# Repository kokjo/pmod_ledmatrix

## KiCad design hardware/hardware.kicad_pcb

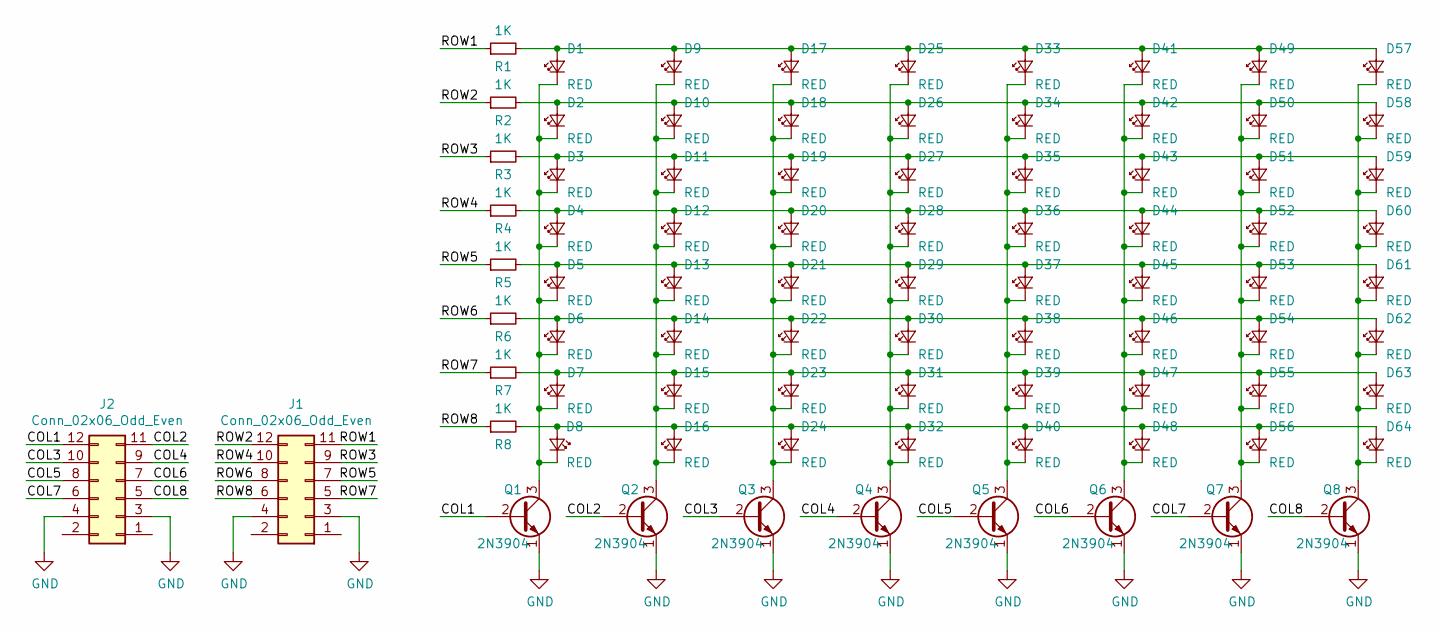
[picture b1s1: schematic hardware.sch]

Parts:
D1, D2, D3, D4, D5, D6, D7, D8, D9, D10, D11, D12, D13, D14, D15, D16, D17, D18, D19, D20, D21, D22, D23, D24, D25, D26, D27, D28, D29, D30, D31, D32, D33, D34, D35, D36, D37, D38, D39, D40, D41, D42, D43, D44, D45, D46, D47, D48, D49, D50, D51, D52, D53, D54, D55, D56, D57, D58, D59, D60, D61, D62, D63, D64: RED; D_0603_1608Metric
J1, J2: Conn_02x06_Odd_Even; PinHeader_2x06_P2.54mm_Horizontal
Q1, Q2, Q3, Q4, Q5, Q6, Q7, Q8: 2N3904; SOT-23
R1, R2, R3, R4, R5, R6, R7, R8: 1K; R_0603_1608Metric

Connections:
/COL1: J2.12, Q1.2 (B)
/COL2: J2.11, Q2.2 (B)
/COL3: J2.10, Q3.2 (B)
/COL4: J2.9, Q4.2 (B)
/COL5: J2.8, Q5.2 (B)
/COL6: J2.7, Q6.2 (B)
/COL7: J2.6, Q7.2 (B)
/COL8: J2.5, Q8.2 (B)
/ROW1: J1.11, R1.1
/ROW2: J1.12, R2.1
/ROW3: J1.9, R3.1
/ROW4: J1.10, R4.1
/ROW5: J1.7, R5.1
/ROW6: J1.8, R6.1
/ROW7: J1.5, R7.1
/ROW8: J1.6, R8.1
GND: J1.3, J1.4, J2.3, J2.4, Q1.1 (E), Q2.1 (E), Q3.1 (E), Q4.1 (E), Q5.1 (E), Q6.1 (E), Q7.1 (E), Q8.1 (E)
unnamed: D1.1 (K), D2.1 (K), D3.1 (K), D4.1 (K), D5.1 (K), D6.1 (K), D7.1 (K), D8.1 (K), Q1.3 (C)
unnamed: D1.2 (A), D9.2 (A), D17.2 (A), D25.2 (A), D33.2 (A), D41.2 (A), D49.2 (A), D57.2 (A), R1.2
unnamed: D9.1 (K), D10.1 (K), D11.1 (K), D12.1 (K), D13.1 (K), D14.1 (K), D15.1 (K), D16.1 (K), Q2.3 (C)
unnamed: D2.2 (A), D10.2 (A), D18.2 (A), D26.2 (A), D34.2 (A), D42.2 (A), D50.2 (A), D58.2 (A), R2.2
unnamed: D3.2 (A), D11.2 (A), D19.2 (A), D27.2 (A), D35.2 (A), D43.2 (A), D51.2 (A), D59.2 (A), R3.2
unnamed: D4.2 (A), D12.2 (A), D20.2 (A), D28.2 (A), D36.2 (A), D44.2 (A), D52.2 (A), D60.2 (A), R4.2
unnamed: D5.2 (A), D13.2 (A), D21.2 (A), D29.2 (A), D37.2 (A), D45.2 (A), D53.2 (A), D61.2 (A), R5.2
unnamed: D6.2 (A), D14.2 (A), D22.2 (A), D30.2 (A), D38.2 (A), D46.2 (A), D54.2 (A), D62.2 (A), R6.2
unnamed: D7.2 (A), D15.2 (A), D23.2 (A), D31.2 (A), D39.2 (A), D47.2 (A), D55.2 (A), D63.2 (A), R7.2
unnamed: D8.2 (A), D16.2 (A), D24.2 (A), D32.2 (A), D40.2 (A), D48.2 (A), D56.2 (A), D64.2 (A), R8.2
unnamed: D17.1 (K), D18.1 (K), D19.1 (K), D20.1 (K), D21.1 (K), D22.1 (K), D23.1 (K), D24.1 (K), Q3.3 (C)
unnamed: D25.1 (K), D26.1 (K), D27.1 (K), D28.1 (K), D29.1 (K), D30.1 (K), D31.1 (K), D32.1 (K), Q4.3 (C)
unnamed: D33.1 (K), D34.1 (K), D35.1 (K), D36.1 (K), D37.1 (K), D38.1 (K), D39.1 (K), D40.1 (K), Q5.3 (C)
unnamed: D41.1 (K), D42.1 (K), D43.1 (K), D44.1 (K), D45.1 (K), D46.1 (K), D47.1 (K), D48.1 (K), Q6.3 (C)
unnamed: D49.1 (K), D50.1 (K), D51.1 (K), D52.1 (K), D53.1 (K), D54.1 (K), D55.1 (K), D56.1 (K), Q7.3 (C)
unnamed: D57.1 (K), D58.1 (K), D59.1 (K), D60.1 (K), D61.1 (K), D62.1 (K), D63.1 (K), D64.1 (K), Q8.3 (C)

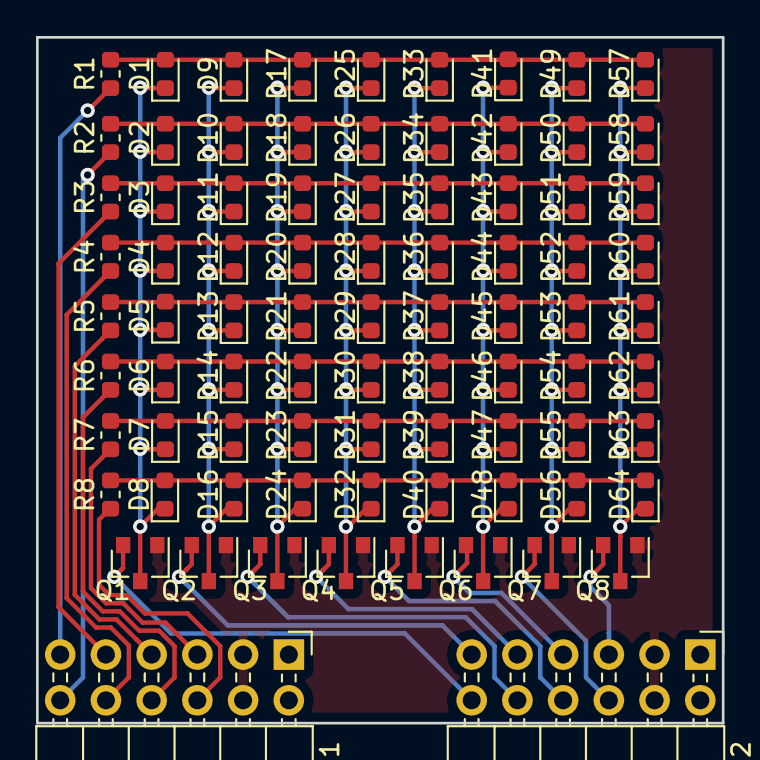
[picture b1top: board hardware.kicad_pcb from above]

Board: 2 copper layers, 38.1 x 38.1 mm, 82 parts (0 on the bottom side), 33 nets.

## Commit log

2019-09-02 Initial commit of pmod_ledmatrix
